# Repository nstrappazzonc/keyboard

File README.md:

# Keyboard Matías

Es mi teclado Ortholinear diseñado y construido por mi, todo el hardware y el diseno es OpenSource (1), la idea de este repositorio es explicarte como se construye uno paso a paso.

1. Los MCU y otros componentes electronicos no son OpenSource.

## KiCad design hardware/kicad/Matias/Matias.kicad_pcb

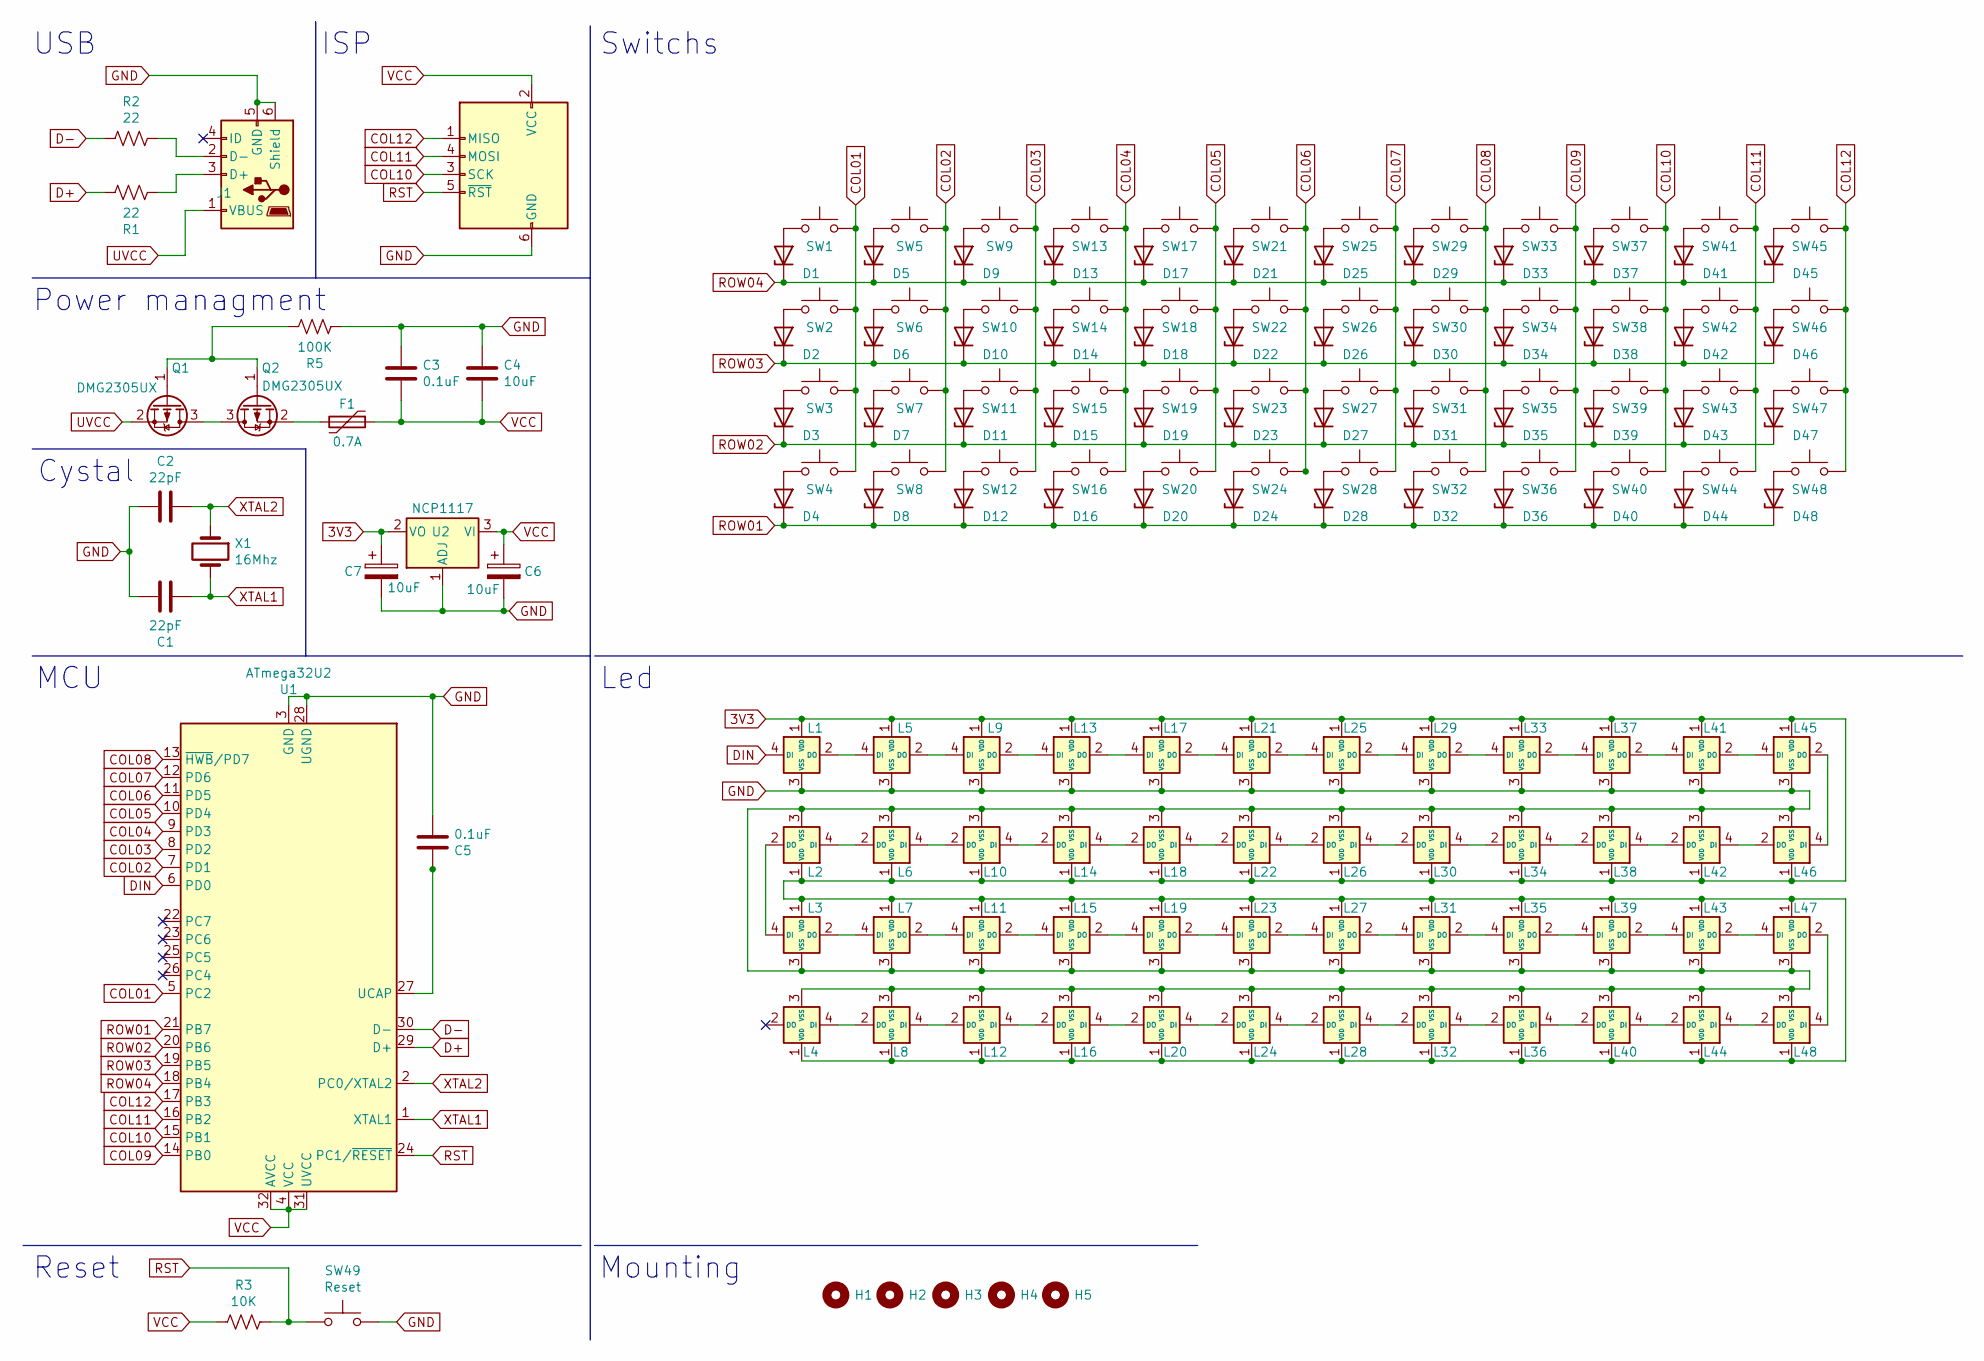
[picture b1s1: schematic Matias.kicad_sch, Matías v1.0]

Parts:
C1, C2: 22pF; C1206
C3, C5: 0.1uF; C1206
C4: 10uF; C1206
C6, C7: 10uF; CP_EIA-3216-18_Kemet-A
D1, D2, D3, D4, D5, D6, D7, D8, D9, D10, D11, D12, D13, D14, D15, D16, D17, D18, D19, D20, D21, D22, D23, D24, D25, D26, D27, D28, D29, D30, D31, D32, D33, D34, D35, D36, D37, D38, D39, D40, D41, D42, D43, D44, D45, D46, D47, D48: 1N47xxA; D1206
F1: 0.7A; R1206
H1, H2, H3, H4, H5: MountingHole; MountingHole_2.2mm_M2
ISP1: AVR-ISP-6; ISP
J1: USB Type B Mini; USB_Micro-B
L1, L2, L3, L4, L5, L6, L7, L8, L9, L10, L11, L12, L13, L14, L15, L16, L17, L18, L19, L20, L21, L22, L23, L24, L25, L26, L27, L28, L29, L30, L31, L32, L33, L34, L35, L36, L37, L38, L39, L40, L41, L42, L43, L44, L45, L46, L47, L48: SK6812MINI; SK6812-MINI-E
Q1, Q2: DMG2305UX; SOT-23
R1, R2: 22; R1206
R3: 10K; R1206
R5: 100K; R1206
SW1, SW2, SW3, SW4, SW5, SW6, SW7, SW8, SW9, SW10, SW11, SW12, SW13, SW14, SW15, SW16, SW17, SW18, SW19, SW20, SW21, SW22, SW23, SW24, SW25, SW26, SW27, SW28, SW29, SW30, SW31, SW32, SW33, SW34, SW35, SW36, SW37, SW38, SW39, SW40, SW41, SW42, SW43, SW44, SW45, SW46, SW47, SW48: Push; Kailh_socket_PG1350
SW49: Reset; SW_SPST_SKQG_WithStem
U1: ATmega32U2; TQFP-32_7x7mm_P0.8mm
U2: NCP1117; SOT-223
X1: 16Mhz; Crystal_SMD_5032-2Pin_5.0x3.2mm

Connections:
3V3: C7.1, L1.1 (VDD), L2.1 (VDD), L3.1 (VDD), L4.1 (VDD), L5.1 (VDD), L6.1 (VDD), L7.1 (VDD), L8.1 (VDD), L9.1 (VDD), L10.1 (VDD), L11.1 (VDD), L12.1 (VDD), L13.1 (VDD), L14.1 (VDD), L15.1 (VDD), L16.1 (VDD), L17.1 (VDD), L18.1 (VDD), L19.1 (VDD), L20.1 (VDD), L21.1 (VDD), L22.1 (VDD), L23.1 (VDD), L24.1 (VDD), L25.1 (VDD), L26.1 (VDD), L27.1 (VDD), L28.1 (VDD), L29.1 (VDD), L30.1 (VDD), L31.1 (VDD), L32.1 (VDD), L33.1 (VDD), L34.1 (VDD), L35.1 (VDD), L36.1 (VDD), L37.1 (VDD), L38.1 (VDD), L39.1 (VDD), L40.1 (VDD), L41.1 (VDD), L42.1 (VDD), L43.1 (VDD), L44.1 (VDD), L45.1 (VDD), L46.1 (VDD), L47.1 (VDD), L48.1 (VDD), U2.2 (VO)
COL01: SW1.2, SW2.2, SW3.2, SW4.2, U1.5 (PC2)
COL02: SW5.2, SW6.2, SW7.2, SW8.2, U1.7 (PD1)
COL03: SW9.2, SW10.2, SW11.2, SW12.2, U1.8 (PD2)
COL04: SW13.2, SW14.2, SW15.2, SW16.2, U1.9 (PD3)
COL05: SW17.2, SW18.2, SW19.2, SW20.2, U1.10 (PD4)
COL06: SW21.2, SW22.2, SW23.2, SW24.2, U1.11 (PD5)
COL07: SW25.2, SW26.2, SW27.2, SW28.2, U1.12 (PD6)
COL08: SW29.2, SW30.2, SW31.2, SW32.2, U1.13 (~HWB/PD7)
COL09: SW33.2, SW34.2, SW35.2, SW36.2, U1.14 (PB0)
COL10: ISP1.3 (SCK), SW37.2, SW38.2, SW39.2, SW40.2, U1.15 (PB1)
COL11: ISP1.4 (MOSI), SW41.2, SW42.2, SW43.2, SW44.2, U1.16 (PB2)
COL12: ISP1.1 (MISO), SW45.2, SW46.2, SW47.2, SW48.2, U1.17 (PB3)
D+: R1.1, U1.29 (D+)
D-: R2.2, U1.30 (D-)
DIN: L1.4 (DI), U1.6 (PD0)
GND: C1.1, C2.2, C3.1, C4.1, C5.2, C6.2, C7.2, ISP1.6 (GND), J1.5 (GND), J1.6 (Shield), L1.3 (VSS), L2.3 (VSS), L3.3 (VSS), L4.3 (VSS), L5.3 (VSS), L6.3 (VSS), L7.3 (VSS), L8.3 (VSS), L9.3 (VSS), L10.3 (VSS), L11.3 (VSS), L12.3 (VSS), L13.3 (VSS), L14.3 (VSS), L15.3 (VSS), L16.3 (VSS), L17.3 (VSS), L18.3 (VSS), L19.3 (VSS), L20.3 (VSS), L21.3 (VSS), L22.3 (VSS), L23.3 (VSS), L24.3 (VSS), L25.3 (VSS), L26.3 (VSS), L27.3 (VSS), L28.3 (VSS), L29.3 (VSS), L30.3 (VSS), L31.3 (VSS), L32.3 (VSS), L33.3 (VSS), L34.3 (VSS), L35.3 (VSS), L36.3 (VSS), L37.3 (VSS), L38.3 (VSS), L39.3 (VSS), L40.3 (VSS), L41.3 (VSS), L42.3 (VSS), L43.3 (VSS), L44.3 (VSS), L45.3 (VSS), L46.3 (VSS), L47.3 (VSS), L48.3 (VSS), R5.2, SW49.2, U1.3 (GND), U1.28 (UGND), U2.1 (ADJ); also elsewhere on the board
unnamed: C5.1, U1.27 (UCAP)
unnamed: D1.2 (A), SW1.1
unnamed: D2.2 (A), SW2.1
unnamed: D3.2 (A), SW3.1
unnamed: D4.2 (A), SW4.1
unnamed: D5.2 (A), SW5.1
unnamed: D6.2 (A), SW6.1
unnamed: D7.2 (A), SW7.1
unnamed: D8.2 (A), SW8.1
unnamed: D9.2 (A), SW9.1
unnamed: D10.2 (A), SW10.1
unnamed: D11.2 (A), SW11.1
unnamed: D12.2 (A), SW12.1
unnamed: D13.2 (A), SW13.1
unnamed: D14.2 (A), SW14.1
unnamed: D15.2 (A), SW15.1
unnamed: D16.2 (A), SW16.1
unnamed: D17.2 (A), SW17.1
unnamed: D18.2 (A), SW18.1
unnamed: D19.2 (A), SW19.1
unnamed: D20.2 (A), SW20.1
unnamed: D21.2 (A), SW21.1
unnamed: D22.2 (A), SW22.1
unnamed: D23.2 (A), SW23.1
unnamed: D24.2 (A), SW24.1
unnamed: D25.2 (A), SW25.1
unnamed: D26.2 (A), SW26.1
unnamed: D27.2 (A), SW27.1
unnamed: D28.2 (A), SW28.1
unnamed: D29.2 (A), SW29.1
unnamed: D30.2 (A), SW30.1
unnamed: D31.2 (A), SW31.1
unnamed: D32.2 (A), SW32.1
unnamed: D33.2 (A), SW33.1
unnamed: D34.2 (A), SW34.1
unnamed: D35.2 (A), SW35.1
unnamed: D36.2 (A), SW36.1
unnamed: D37.2 (A), SW37.1
unnamed: D38.2 (A), SW38.1
unnamed: D39.2 (A), SW39.1
unnamed: D40.2 (A), SW40.1
unnamed: D41.2 (A), SW41.1
unnamed: D42.2 (A), SW42.1
unnamed: D43.2 (A), SW43.1
unnamed: D44.2 (A), SW44.1
unnamed: D45.2 (A), SW45.1
unnamed: D46.2 (A), SW46.1
unnamed: D47.2 (A), SW47.1
unnamed: D48.2 (A), SW48.1
unnamed: F1.2, Q2.2 (S)
unnamed: J1.2 (D-), R2.1
unnamed: J1.3 (D+), R1.2
unnamed: L1.2 (DO), L5.4 (DI)
unnamed: L2.2 (DO), L3.4 (DI)
unnamed: L2.4 (DI), L6.2 (DO)
unnamed: L3.2 (DO), L7.4 (DI)
unnamed: L4.4 (DI), L8.2 (DO)
unnamed: L5.2 (DO), L9.4 (DI)
unnamed: L6.4 (DI), L10.2 (DO)
unnamed: L10.4 (DI), L14.2 (DO)
unnamed: L11.2 (DO), L15.4 (DI)
unnamed: L7.2 (DO), L11.4 (DI)
unnamed: L8.4 (DI), L12.2 (DO)
unnamed: L12.4 (DI), L16.2 (DO)
unnamed: L13.2 (DO), L17.4 (DI)
unnamed: L9.2 (DO), L13.4 (DI)
unnamed: L14.4 (DI), L18.2 (DO)
unnamed: L15.2 (DO), L19.4 (DI)
unnamed: L16.4 (DI), L20.2 (DO)
unnamed: L17.2 (DO), L21.4 (DI)
unnamed: L18.4 (DI), L22.2 (DO)
unnamed: L19.2 (DO), L23.4 (DI)
unnamed: L20.4 (DI), L24.2 (DO)
unnamed: L21.2 (DO), L25.4 (DI)
unnamed: L22.4 (DI), L26.2 (DO)
unnamed: L23.2 (DO), L27.4 (DI)
unnamed: L24.4 (DI), L28.2 (DO)
unnamed: L25.2 (DO), L29.4 (DI)
unnamed: L26.4 (DI), L30.2 (DO)
unnamed: L27.2 (DO), L31.4 (DI)
unnamed: L28.4 (DI), L32.2 (DO)
unnamed: L29.2 (DO), L33.4 (DI)
unnamed: L30.4 (DI), L34.2 (DO)
unnamed: L31.2 (DO), L35.4 (DI)
unnamed: L32.4 (DI), L36.2 (DO)
unnamed: L33.2 (DO), L37.4 (DI)
unnamed: L34.4 (DI), L38.2 (DO)
unnamed: L35.2 (DO), L39.4 (DI)
unnamed: L36.4 (DI), L40.2 (DO)
unnamed: L37.2 (DO), L41.4 (DI)
unnamed: L38.4 (DI), L42.2 (DO)
unnamed: L39.2 (DO), L43.4 (DI)
unnamed: L40.4 (DI), L44.2 (DO)
unnamed: L41.2 (DO), L45.4 (DI)
unnamed: L42.4 (DI), L46.2 (DO)
unnamed: L43.2 (DO), L47.4 (DI)
unnamed: L44.4 (DI), L48.2 (DO)
unnamed: L45.2 (DO), L46.4 (DI)
unnamed: L47.2 (DO), L48.4 (DI)
unnamed: Q1.1 (G), Q2.1 (G), R5.1
unnamed: Q1.3 (D), Q2.3 (D)
ROW01: D4.1 (K), D8.1 (K), D12.1 (K), D16.1 (K), D20.1 (K), D24.1 (K), D28.1 (K), D32.1 (K), D36.1 (K), D40.1 (K), D44.1 (K), D48.1 (K), U1.21 (PB7)
ROW02: D3.1 (K), D7.1 (K), D11.1 (K), D15.1 (K), D19.1 (K), D23.1 (K), D27.1 (K), D31.1 (K), D35.1 (K), D39.1 (K), D43.1 (K), D47.1 (K), U1.20 (PB6)
ROW03: D2.1 (K), D6.1 (K), D10.1 (K), D14.1 (K), D18.1 (K), D22.1 (K), D26.1 (K), D30.1 (K), D34.1 (K), D38.1 (K), D42.1 (K), D46.1 (K), U1.19 (PB5)
ROW04: D1.1 (K), D5.1 (K), D9.1 (K), D13.1 (K), D17.1 (K), D21.1 (K), D25.1 (K), D29.1 (K), D33.1 (K), D37.1 (K), D41.1 (K), D45.1 (K), U1.18 (PB4)
RST: ISP1.5 (~RST), R3.2, SW49.1, U1.24 (PC1/~RESET); also elsewhere on the board
UVCC: J1.1 (VBUS), Q1.2 (S)
VCC: C3.2, C4.2, C6.1, F1.1, ISP1.2 (VCC), R3.1, U1.4 (VCC), U1.31 (UVCC), U1.32 (AVCC), U2.3 (VI)
XTAL1: C1.2, U1.1 (XTAL1), X1.2
XTAL2: C2.1, U1.2 (PC0/XTAL2), X1.1

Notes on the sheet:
USB
Power managment
MCU
Reset
Mounting
Led
ISP
Switchs
Cystal

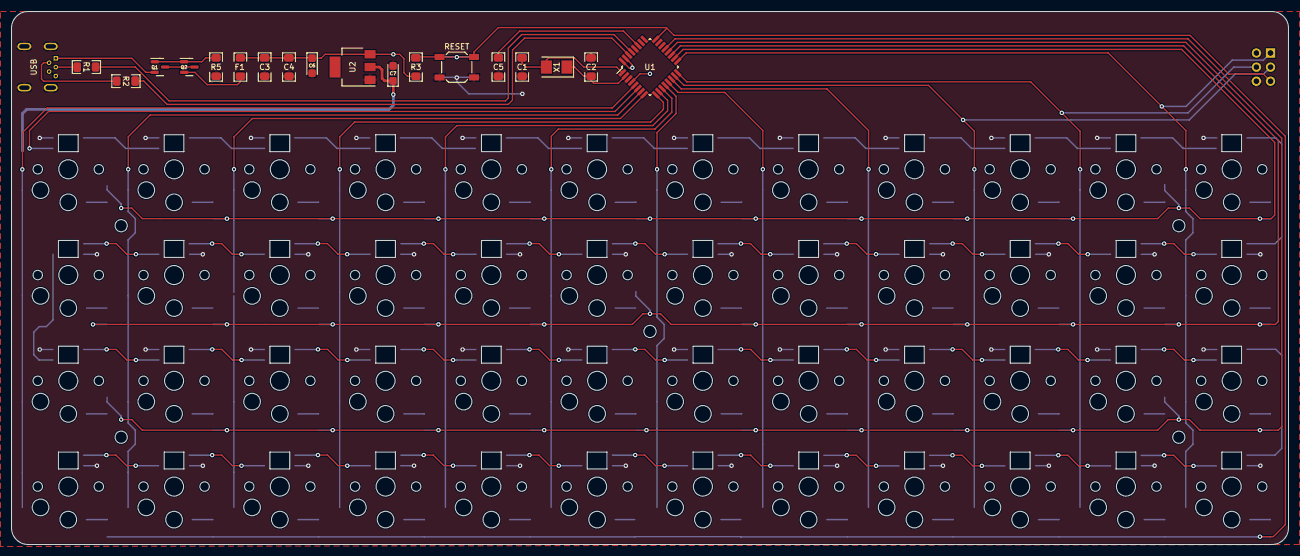
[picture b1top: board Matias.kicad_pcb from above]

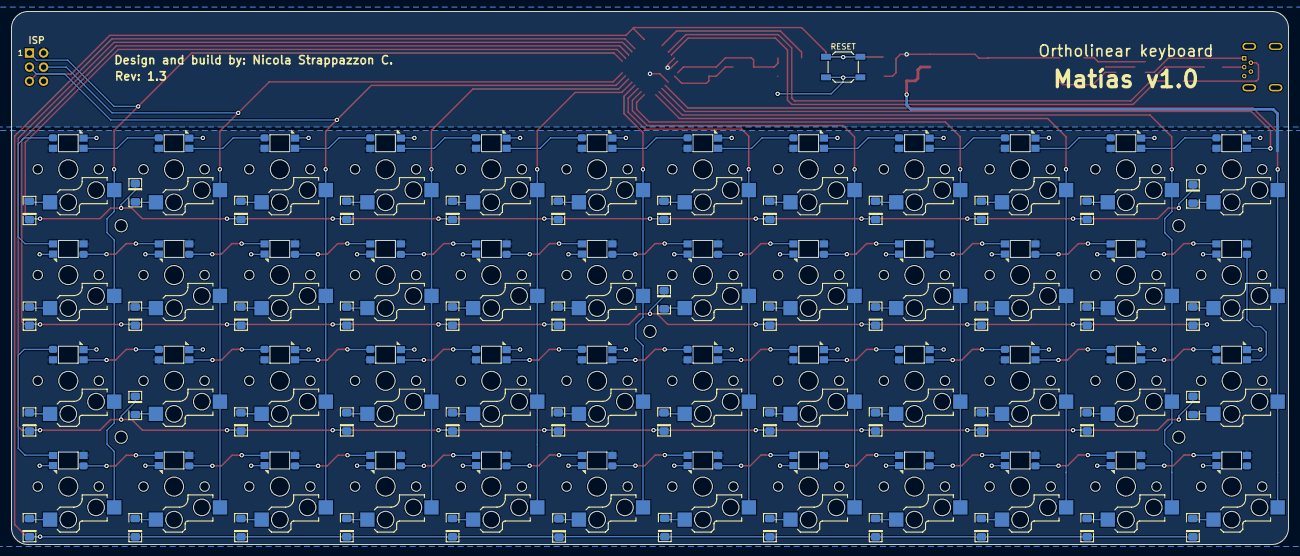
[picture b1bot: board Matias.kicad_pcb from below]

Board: 2 copper layers, 230.0 x 96.0 mm, 170 parts (50 on the bottom side), 127 nets.

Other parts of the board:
SW49#2: Reset; SW_SPST_SKQG_WithStem

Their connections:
GND: SW49#2.2; also elsewhere on the board
RST: SW49#2.1; also elsewhere on the board

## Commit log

2022-07-01 feat(firmware) first version.
2022-07-01 feat(kicad) add project
2022-07-01 feat(bom) add file and datasheets.
2022-07-22 feat(doc) update.
2022-07-23 add todo list
